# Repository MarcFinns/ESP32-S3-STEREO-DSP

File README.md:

# ESP32-S3 STEREO DSP BOARD

A board with ESP32-S3, ADC, DAC, LCD display for audio application and beyond. 
While these components can be connected in principle on any breakout board for prototyping, proper power decoupling and series terminator resistors are necessary to limit noise and interference.
This board ensures that all signals are appropriately decoupled and routed, on a single layer PCB.

The board was used to develop the [PiratESP32 FM RDS STEREO ENCODER](https://github.com/MarcFinns/PiratESP32-FM-RDS-STEREO-ENCODER)

## Features

### ESP32 Board
- **ESP32-S3 N16R8** with dual-core processor with SIMD (vector) instructions to boost DSP applications
- **ADC**: PCM1808 I2S audio ADC (24 bit, up to 96 kHz sample rate, I2S slave)
- **DAC**: PCM5102A I2S audio DAC (16/24/32 bit, up to 192 kHz sample rate, I2S slave)
- **Display (optional)** ILI9341 320×240 TFT LCD (SPI interface)
- **GPIO connector** for LED/buttons or anything else

## Pin Configuration

### I2S Audio
```
Master Clock (shared):  GPIO 8  (tested at 24.576 MHz MCLK)

ADC Input:
  BCK  (Bit Clock):     GPIO 4
  LRCK (Word Select):   GPIO 6
  DIN  (Serial Data):   GPIO 5

DAC Output:
  BCK  (Bit Clock):     GPIO 9
  LRCK (Word Select):   GPIO 11
  DOUT (Serial Data):   GPIO 10

ILI9341 TFT Display
	SCK  (SPI Clock):       GPIO 40
	MOS	I (SPI Data):        GPIO 41
	DC   (Data/Command):    GPIO 42
	CS   (Chip Select):     GPIO 1
	RST  (Reset):           GPIO 2

GPIO Connector
	3V3
	GPIO39
	GPIO38
	GPIO48
	GPIO47
	GPIO21
```

## Important notes

- Some PCM1808 ADC breakout boards have a **very aggressive low pass filter** (the filter is optional from the datasheet, and they chose a wrong capacitor value). This results in a lowpass filter at 6Khz! If sound is muffled, you can just desolder the caps (or break them, it is fine). See picture

- The board is designed to be powered 
both from USB on the ESP and from the Vin, 
without conflicts. However, to enable the board 
to work when powered via USB, it is often 
necessary to connect a jumper on the ESP32-
S3 board that enables 5V out. 
The location of the jumper depends on 
the flavour of the development board! **Look it up!**

- The board can be powered with a power supply connected to the Vin connector (12v max) so that it can work standalone / when not connected to a PC via USB. To that end, a LDO is included in the schematic. It can be skipped if only USB power is necessary. The LDO (AMS1117 family) can be either ADJ or 5V fixed version. A solder jumper on the PCB is provided to select the version. If fixed, connect SJ1 jumper to GND. If adj, connect to R divider. **If left not connected, bad things will happen**

- The PCB and schematic in the folder are correct. The pictures are of my first prototybe that had some mistakes, corrected later!

- SMD components are 0805 size. If uneasy with SMD, one could just redesign the PCB with through hole, keeping the schematic and even the routing - just make it larger

## Breakout boards

The following breakout boards are matching the PCB.
If different ones are used, schematic is still valid but re-routing of the PCB might become necessary.

- [ILI9341 Display](https://nl.aliexpress.com/item/32913890225.html)
- [PCM1808 ADC breakout board](https://nl.aliexpress.com/item/1005006749086540.html)
- [PCM5102A DAC breakout board](https://nl.aliexpress.com/item/1005009648364414.html)
- [ESP32-S3 N16R8](https://nl.aliexpress.com/item/1005007319706057.html)

## References

- [PCM1808 ADC datasheet](https://www.ti.com/lit/ds/symlink/pcm1808.pdf)
- [PCM5102A DAC datasheet](https://www.ti.com/lit/ds/symlink/pcm5102a.pdf)
- [ESP32-S3 documentation](https://www.espressif.com/sites/default/files/documentation/esp32-s3_technical_reference_manual_en.pdf)
- [ESP32 I2S Documentation](https://docs.espressif.com/projects/esp-idf/en/latest/esp32/api-reference/peripherals/i2s.html)

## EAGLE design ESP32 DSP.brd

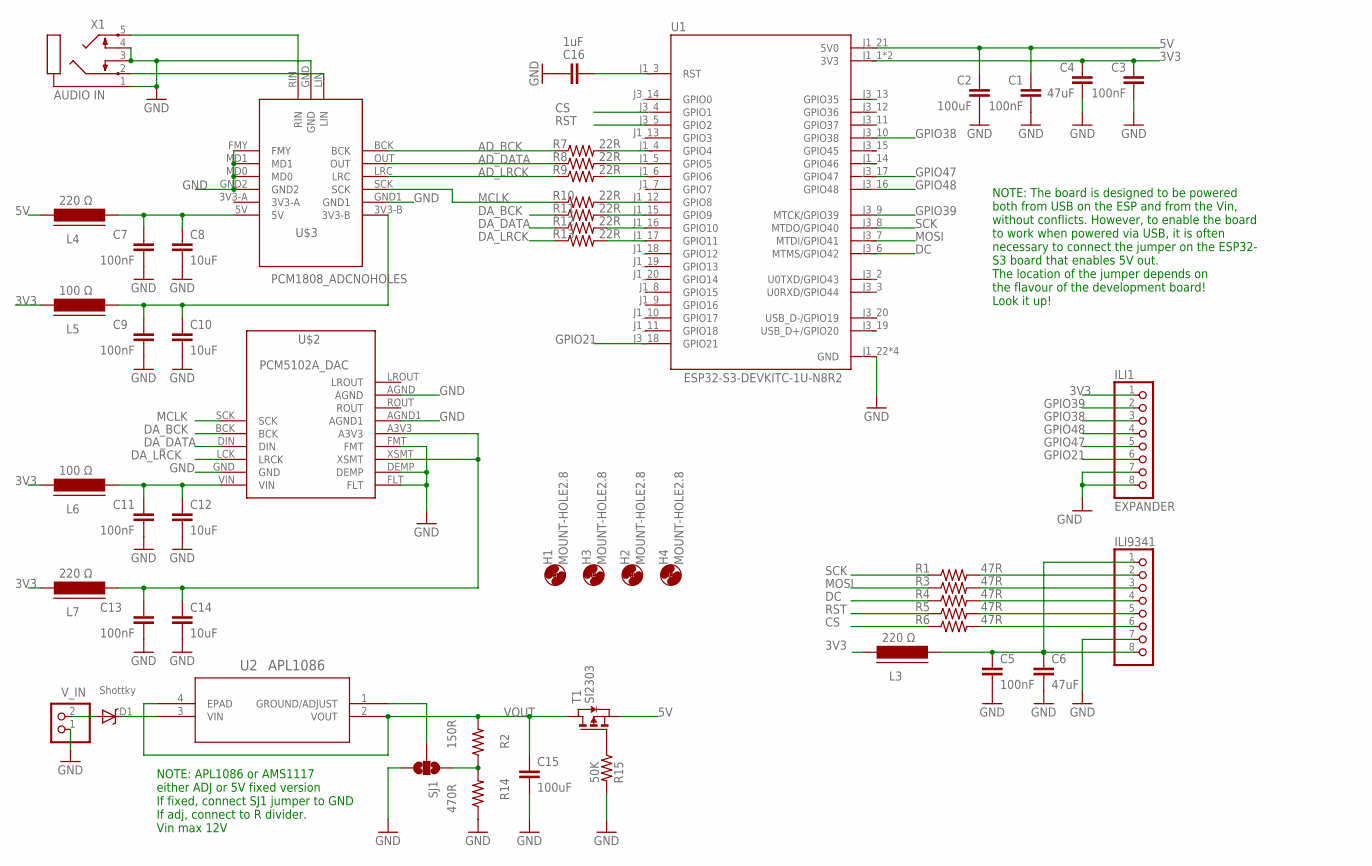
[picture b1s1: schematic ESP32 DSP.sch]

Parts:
C1, C3, C5, C7, C9, C11, C13: 100nF; C0805
C2, C15: 100uF; C0805
C4, C6: 47uF; C0805
C8, C10, C12, C14: 10uF; C0805
C16: 1uF; C0805
D1: Shottky; SMA-403D
H1, H2, H3, H4: MOUNT-HOLE2.8; 2,8
ILI1: EXPANDER; 1X08
ILI9341: PINHD-1X8; 1X08
L3, L4, L7: 220 Ω; FB805
L5, L6: 100 Ω; FB805
R1, R3, R4, R5, R6: 47R; M0805
R2: 150R; M0805
R7, R8, R9, R10, R11, R12, R13: 22R; M0805
R14: 470R; M0805
R15: 50K; M0805
SJ1: SOLDERJUMPER_2WAYS; SJ_3
T1: SI2303; SOT-23
U1: ESP32-S3-DEVKITC-1U-N8R2; XCVR_ESP32-S3-DEVKITC-1U-N8R2
U2: APL1086; SOT_AMS_ADS
U$2: PCM5102A_DAC; I2S_PCM_5100_SOUNDCARD
U$3: PCM1808_ADCNOHOLES; CMJCU-1808-NOHOLES
V_IN: 5V; 1X02
X1: AUDIO IN; STX3100

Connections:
3V3: C3.1, C4.1, ILI1.1, L3.1, L5.1, L6.1, L7.1, U1.J1_1 (3V3), U1.J1_2 (3V3)
5V: C1.1, C2.1, L4.1, T1.2 (S), U1.J1_21 (5V0)
AD_BCK: R7.1, U$3.BCK
AD_DATA: R8.1, U$3.OUT
AD_LRCK: R9.1, U$3.LRC
CS: R6.1, U1.J3_4 (GPIO1)
DA_BCK: R11.1, U$2.BCK
DA_DATA: R12.1, U$2.DIN
DA_LRCK: R13.1, U$2.LCK (LRCK)
DC: R4.1, U1.J3_6 (MTMS/GPIO42)
GND: C1.2, C2.2, C3.2, C4.2, C5.2, C6.2, C7.2, C8.2, C9.2, C10.2, C11.2, C12.2, C13.2, C14.2, C15.2, C16.2, ILI1.7, ILI1.8, ILI9341.7, R14.1, R15.2, SJ1.3, U1.J1_22 (GND), U1.J3_1 (GND), U1.J3_21 (GND), U1.J3_22 (GND), U$2.AGND, U$2.AGND1, U$2.DEMP, U$2.FLT, U$2.FMT, U$2.GND, U$3.FMY, U$3.GND, U$3.GND1, U$3.GND2, U$3.MD0, U$3.MD1, V_IN.1, X1.1, X1.3, X1.4
GPIO21: ILI1.6, U1.J3_18 (GPIO21)
GPIO38: ILI1.3, U1.J3_10 (GPIO38)
GPIO39: ILI1.2, U1.J3_9 (MTCK/GPIO39)
GPIO47: ILI1.5, U1.J3_17 (GPIO47)
GPIO48: ILI1.4, U1.J3_16 (GPIO48)
MCLK: R10.1, U$2.SCK, U$3.SCK
MOSI: R3.1, U1.J3_7 (MTDI/GPIO41)
unnamed: ILI9341.2, R1.2
unnamed: ILI9341.3, R3.2
unnamed: ILI9341.4, R4.2
unnamed: ILI9341.5, R5.2
unnamed: ILI9341.6, R6.2
unnamed: C11.1, C12.1, L6.2, U$2.VIN
unnamed: C13.1, C14.1, L7.2, U$2.A3V3, U$2.XSMT
unnamed: U$3.RIN, X1.5
unnamed: U$3.LIN, X1.2
unnamed: R2.1, R14.2, SJ1.1
unnamed: D1.C, U2.3 (VIN)
unnamed: C16.1, U1.J1_3 (RST)
unnamed: SJ1.2, U2.1 (GROUND/ADJUST)
unnamed: R15.1, T1.3 (G)
unnamed: R7.2, U1.J1_4 (GPIO4)
unnamed: R8.2, U1.J1_5 (GPIO5)
unnamed: R9.2, U1.J1_6 (GPIO6)
unnamed: R10.2, U1.J1_12 (GPIO8)
unnamed: R11.2, U1.J1_15 (GPIO9)
unnamed: R12.2, U1.J1_16 (GPIO10)
unnamed: R13.2, U1.J1_17 (GPIO11)
unnamed: C9.1, C10.1, L5.2, U$3.3V3-B
unnamed: C7.1, C8.1, L4.2, U$3.5V
unnamed: C5.1, C6.1, ILI9341.1, ILI9341.8, L3.2
RST: R5.1, U1.J3_5 (GPIO2)
SCK: R1.1, U1.J3_8 (MTDO/GPIO40)
VOUT: C15.1, R2.2, T1.1 (D), U2.2 (VOUT), U2.4 (EPAD)
V_IN: D1.A, V_IN.2

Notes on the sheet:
NOTE: APL1086 or AMS1117 either ADJ or 5V fixed version If fixed, connect SJ1 jumper to GND If adj, connect to R divider. Vin max 12V
NOTE: The board is designed to be powered both from USB on the ESP and from the Vin, without conflicts. However, to enable the board to work when powered via USB, it is often necessary to connect the jumper on the ESP32- S3 board that enables 5V out. The location of the jumper depends on the flavou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

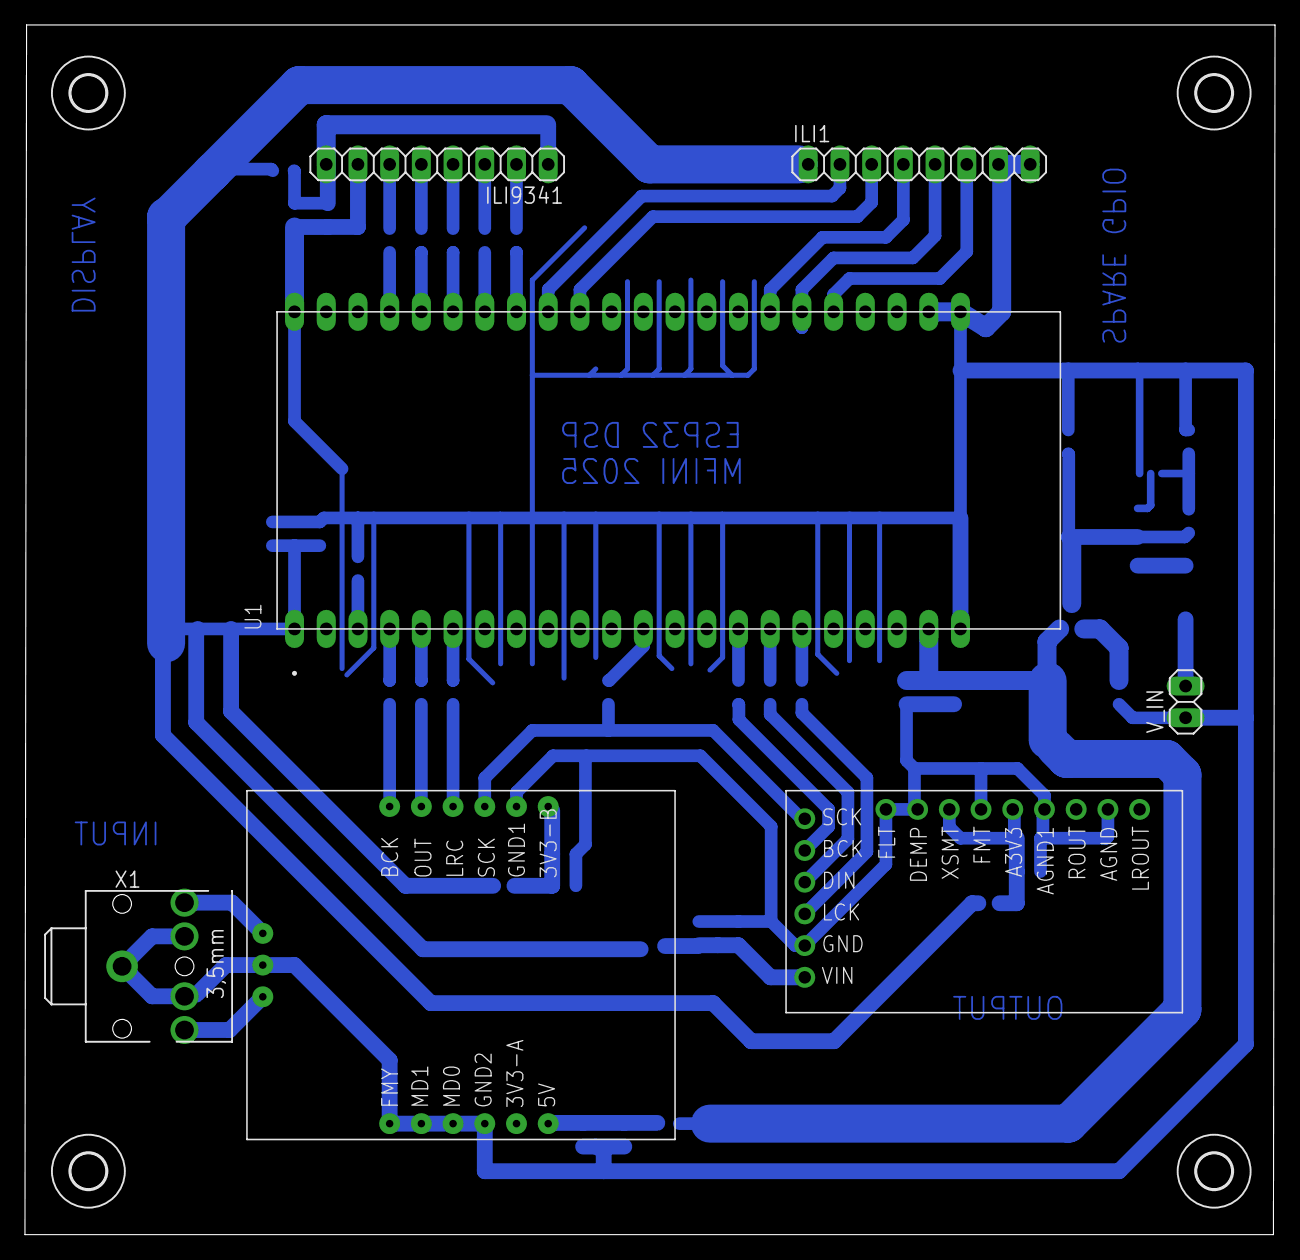
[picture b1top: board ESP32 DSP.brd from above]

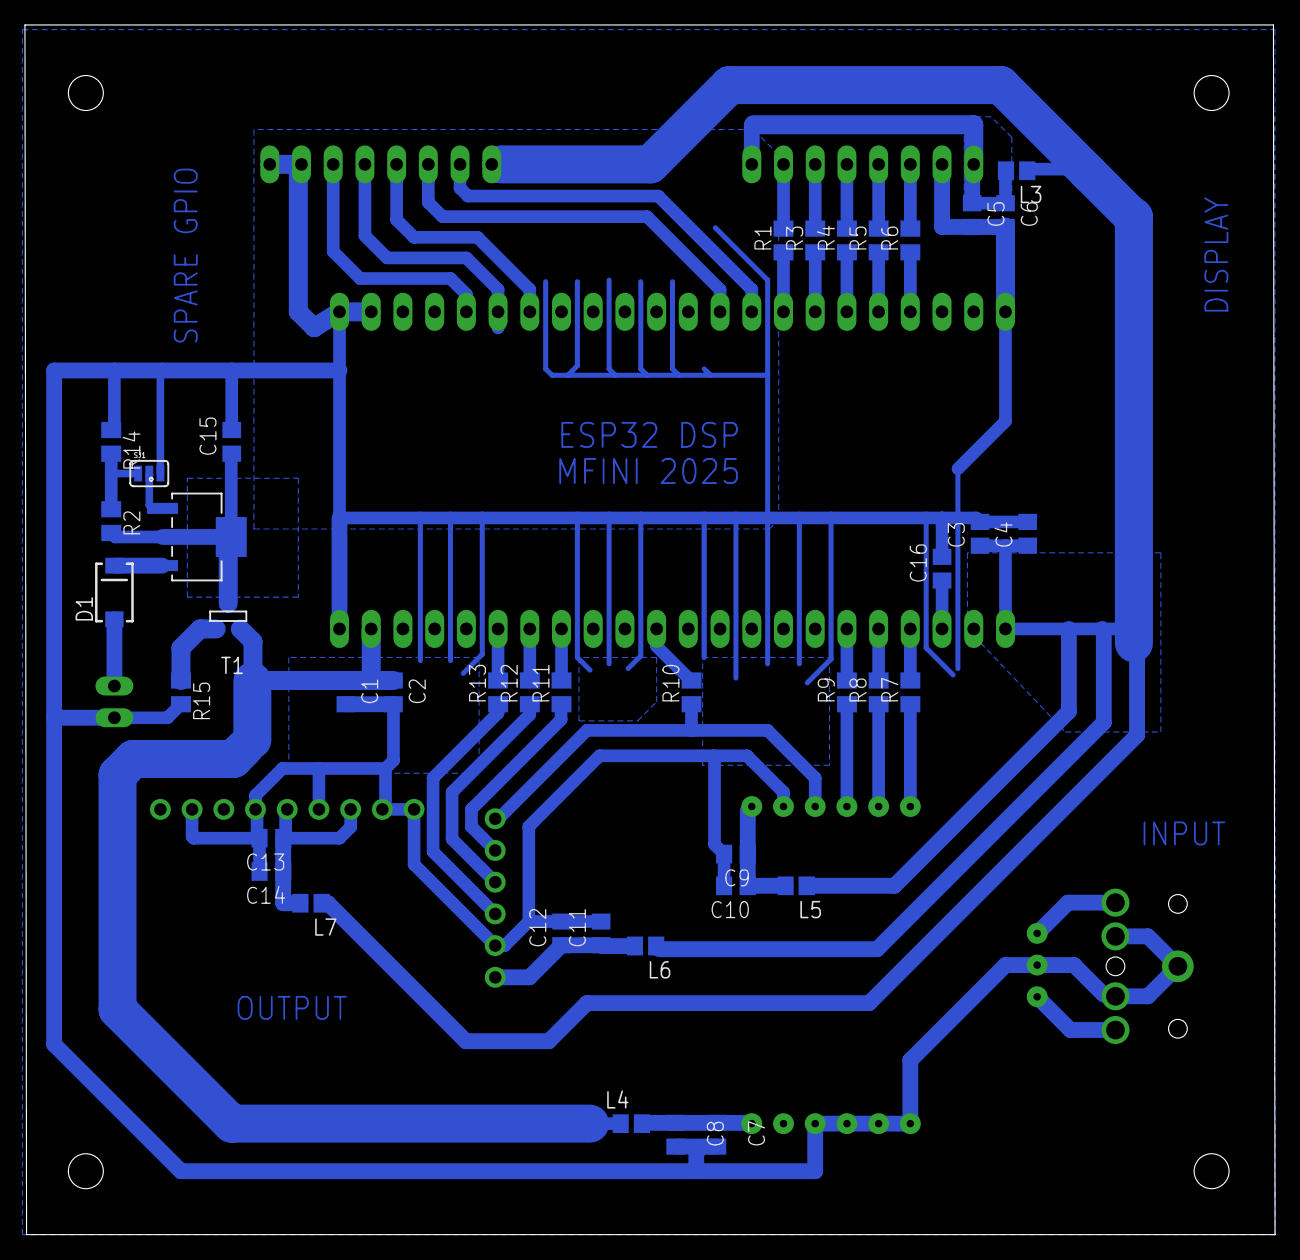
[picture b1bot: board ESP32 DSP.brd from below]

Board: 2 copper layers, 100.1 x 96.9 mm, 51 parts (40 on the bottom side), 46 nets.

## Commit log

2025-10-18 Initial commit: ESP32-S3 Stereo DSP project files
2025-10-18 Fix heading format for Boards section in README
    Corrected heading formatting for 'Boards' section.
2025-10-18 Rename 'Boards' section to 'Breakout boards'
    Updated section title from 'Boards' to 'Breakout boards' in README.
2025-10-22 Update README with project reference
    Added a reference to the PiratESP32 FM RDS Stereo Encoder project.
2025-10-22 Add image of PCB to README
    Added an image to the README to show the PCB in action.
2025-10-22 Fix formatting of ADC feature in README.md
2025-10-23 Update wording for noise and interference clarification
2026-01-12 Create AUDIO_DSP_TEST_48_192_PASSTHROUGH.ino
    A simple sketch to test the board.
2026-01-12 Add ESP32-S3 Audio DSP sketch for upsampling
    Added an ESP32-S3 Audio DSP sketch for 48kHz to 192kHz audio processing with I2S configuration and cubic Hermite interpolation for upsampling.

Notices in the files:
parts and their libraries:
SparkFun-Passives: Licensing: CC v3.0 Share-Alike You are welcome to use this library for commercial purposes.
COPYRIGHT: Copyright (C) 2025 Ultra Librarian. All rights reserved.
